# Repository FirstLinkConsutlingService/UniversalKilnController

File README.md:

# UniversalKilnController
A Hardware/Software project to control devices of the KILN persuasion ( temperature and cooking time manager) 

Test1

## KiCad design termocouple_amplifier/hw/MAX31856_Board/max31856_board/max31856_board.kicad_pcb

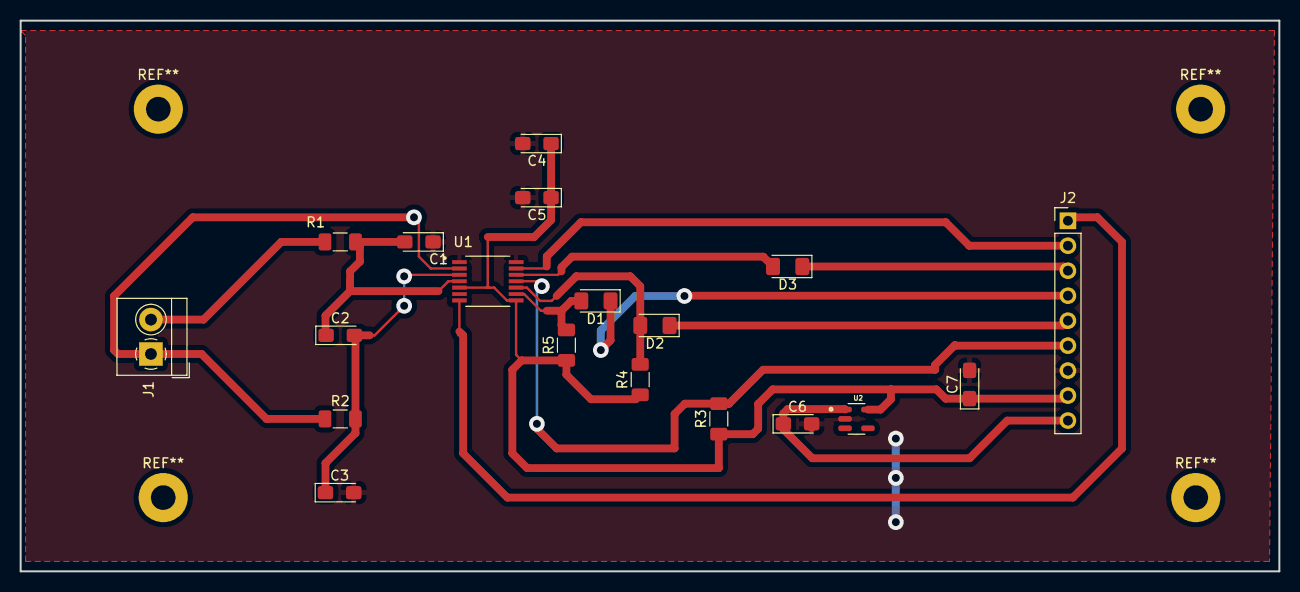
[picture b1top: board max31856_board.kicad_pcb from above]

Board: 2 copper layers, 128.0 x 56.0 mm, 19 parts (0 on the bottom side), 16 nets.

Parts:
C1, C3: 0.01uF; CP_EIA-3216-10_Kemet-I_Pad1.58x1.35mm_HandSolder
C2, C4, C5: 0.1uF; CP_EIA-3216-10_Kemet-I_Pad1.58x1.35mm_HandSolder
C6, C7: 10uF; CP_EIA-3216-10_Kemet-I_Pad1.58x1.35mm_HandSolder
D1, D2, D3: 1N4148; D_1206_3216Metric_Pad1.42x1.75mm_HandSolder
J1: Screw_Terminal_01x02; TerminalBlock_4Ucon_1x02_P3.50mm_Horizontal
J2: Conn_01x09_Male; PinHeader_1x09_P2.54mm_Vertical
R1, R2: 100; R_1206_3216Metric_Pad1.30x1.75mm_HandSolder
R3, R4, R5: 10K; R_1206_3216Metric_Pad1.30x1.75mm_HandSolder
U1: MAX31856MUD+T; SOP65P640X110-14N
U2: MIC5225-3.3YM5-TR; SOT95P280X145-5N

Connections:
+3.3V: C4.1, C5.1, C7.1, J2.8, R3.1, R4.1, R5.1, U1.5 (AVDD), U1.8 (DVDD), U2.5 (OUT)
/SCK: D2.1 (K), J2.5
/SDI: D3.1 (K), J2.3
/SDO: J2.6, R3.2, U1.11 (SDO)
/T+: C1.2, C2.1, R1.2, U1.4 (T+)
/T-: C2.2, C3.1, R2.2, U1.3 (T-)
/THERM-: J1.1, R2.1, U1.2 (BIAS)
/VIN: C6.1, J2.9, U2.1 (IN), U2.3 (EN)
/~CS: D1.1 (K), J2.4
/~DRDY: J2.1, U1.7 (~DRDY)
/~FAULT: J2.2, U1.13 (~FAULT)
GNDD: C1.1, C3.2, C4.2, C5.2, C6.2, C7.2, J2.7, U1.1 (AGND), U1.14 (DGND), U2.2 (GND)
unnamed: D1.2 (A), R5.2, U1.9 (~CS)
unnamed: D2.2 (A), R4.2, U1.10 (SCK)
unnamed: D3.2 (A), U1.12 (SDI)
unnamed: J1.2, R1.1

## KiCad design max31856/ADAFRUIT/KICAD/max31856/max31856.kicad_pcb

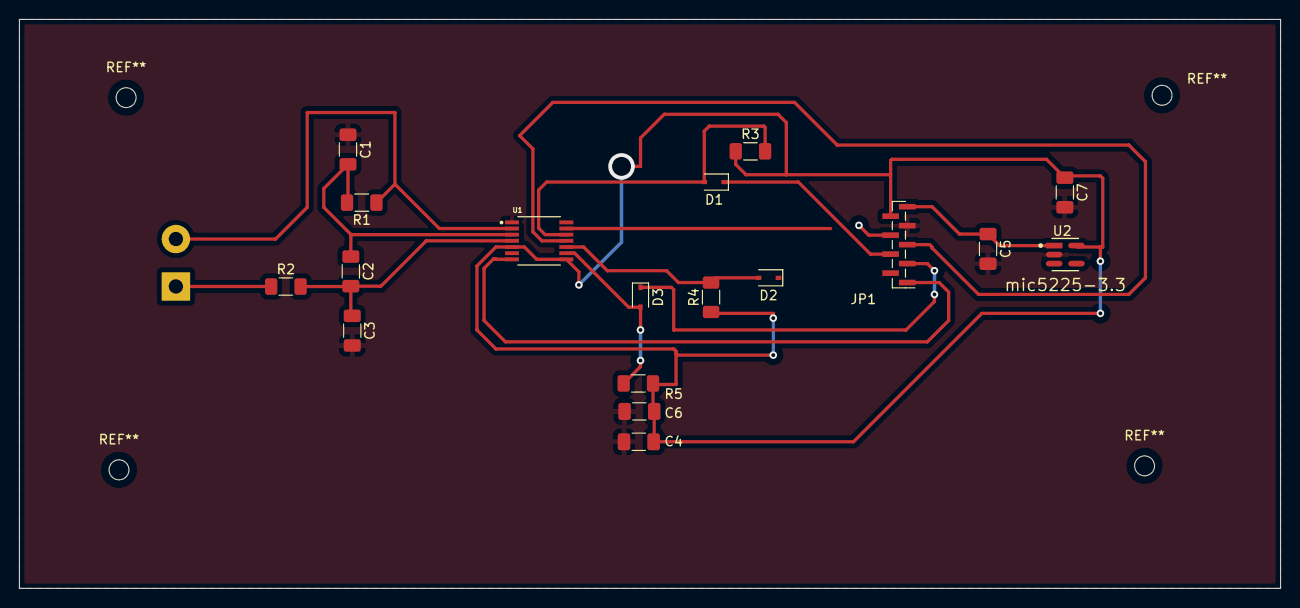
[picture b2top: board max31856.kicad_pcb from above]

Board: 2 copper layers, 133.0 x 60.0 mm, 19 parts (1 on the bottom side), 16 nets.

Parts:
C1, C2, C3: 0.01uF; C_1206_3216Metric_Pad1.33x1.80mm_HandSolder
C4, C6: 0.1uF; C_1206_3216Metric_Pad1.33x1.80mm_HandSolder
C5, C7: 10uF; C_1206_3216Metric_Pad1.33x1.80mm_HandSolder
D1, D2, D3: 1N4148; D_SOD-323
JP1: HEADER-1X970MIL; PinHeader_1x09_P1.00mm_Vertical_SMD_Pin1Left
R1, R2: 100; R_1206_3216Metric_Pad1.30x1.75mm_HandSolder
R3, R4, R5: 10K; R_1206_3216Metric_Pad1.30x1.75mm_HandSolder
U1: MAX31856; SOP65P640X110-14N
U2: mic5225-3.3; Microchip_Technology-SOT23-5LD-PL-1-0-0-IPC_A
X1: 3.5mm term; Altech_AK300_1x02_P5.00mm_45-Degree

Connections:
+3V3: C4.1, C6.1, C7.1, JP1.8, R3.1, R4.1, R5.1, U1.5 (AVDD), U1.8 (DVDD), U2.5 (OUT)
/DRDY: JP1.1, U1.7 (~DRDY)
GNDD: C1.1, C3.2, C4.2, C5.2, C6.2, C7.2, JP1.7, U1.1 (AGND), U2.2 (GND)
unnamed: C1.2, C2.1, R1.2, U1.3 (T-)
unnamed: C2.2, C3.1, R2.2, U1.4 (T+)
unnamed: D1.1 (K), JP1.4
unnamed: D1.2 (A), R3.2, U1.12 (SDI)
unnamed: D2.1 (K), JP1.6 (2)
unnamed: D2.2 (A), R4.2, U1.10 (SCK)
unnamed: D3.1 (K), JP1.3
unnamed: D3.2 (A), R5.2, U1.9 (~CS)
unnamed: JP1.2 (6), U1.13 (~FAULT)
unnamed: JP1.5, U1.11 (SDO)
unnamed: R1.1, U1.2 (BIAS), X1.2
unnamed: R2.1, X1.1
VDD: C5.1, JP1.9, U2.1 (IN), U2.3 (EN)

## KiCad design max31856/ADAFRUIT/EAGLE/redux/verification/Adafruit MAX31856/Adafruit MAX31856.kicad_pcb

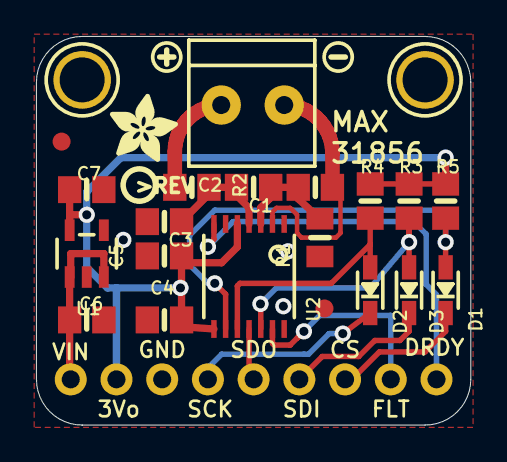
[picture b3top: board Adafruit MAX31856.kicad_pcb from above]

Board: 2 copper layers, 24.1 x 21.6 mm, 28 parts (1 on the bottom side), 16 nets.

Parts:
C1: 0.01uF; 0805_10MGAP
C2, C4, C5: 0.1uF; 0805-NO
C3: 0.01uF; 0805-NO
C6, C7: 10uF; 0805-NO
D1, D2, D3: 1N4148; SOD-323
FID1, FID2: FIDUCIAL""; FIDUCIAL_1MM
JP1: 1X09_ROUND_70
R1, R2: 100; 0805-NO
R3, R4, R5: 10K; 0805-NO
U1: mic5225-3.3; SOT23-5
U2: MAX31856; TSSOP14
U$1: PCBFEAT-REV-040
U$13, U$14: MOUNTINGHOLE2.5; MOUNTINGHOLE_2.5_PLATED
U$23: SYMBOL_PLUS
U$24: SYMBOL_MINUS
U$25: ADAFRUIT_3.5MM
U$26: ADAFRUIT_TEXT_20MM
X1: 3.5mm term; TERMBLOCK_1X2-3.5MM

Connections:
3.3V: C4.1, C5.1, C7.1, JP1.8, R3.2, R4.2, R5.2, U1.5, U2.5, U2.8
DRDY: JP1.1, U2.7
GND: C1.1, C3.2, C4.2, C5.2, C6.2, C7.2, JP1.7, U1.2, U2.1, U2.14
SCK: D2.C, JP1.6
SCK_3V: D2.A, R4.1, U2.10
SDI: D3.C, JP1.4
SDO: JP1.5, U2.11
SDO_3V: D3.A, R3.1, U2.12
T+: C2.2, C3.1, R2.2, U2.4
T-: C1.2, C2.1, R1.2, U2.3
THERM+: R2.1, X1.1
THERM-: R1.1, U2.2, X1.2
VIN: C6.1, JP1.9, U1.1, U1.3
~CS_3V: D1.A, R5.1, U2.9
~CS: D1.C, JP1.3
~FAULT: JP1.2, U2.13

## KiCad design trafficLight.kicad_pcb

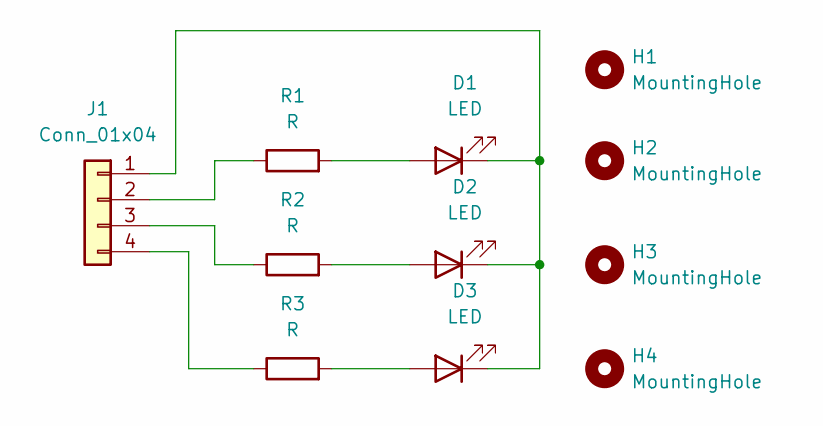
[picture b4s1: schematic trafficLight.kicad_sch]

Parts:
D1, D2, D3: LED; LED_D5.0mm
H1, H2, H3, H4: MountingHole; MountingHole_2.5mm
J1: Conn_01x04; JST_PH_B4B-PH-K_1x04_P2.00mm_Vertical
R1, R2, R3: R; R_Axial_DIN0207_L6.3mm_D2.5mm_P10.16mm_Horizontal

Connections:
unnamed: D1.1 (K), D2.1 (K), D3.1 (K), J1.1
unnamed: D1.2 (A), R1.2
unnamed: D2.2 (A), R2.2
unnamed: D3.2 (A), R3.2
unnamed: J1.2, R1.1
unnamed: J1.3, R2.1
unnamed: J1.4, R3.1

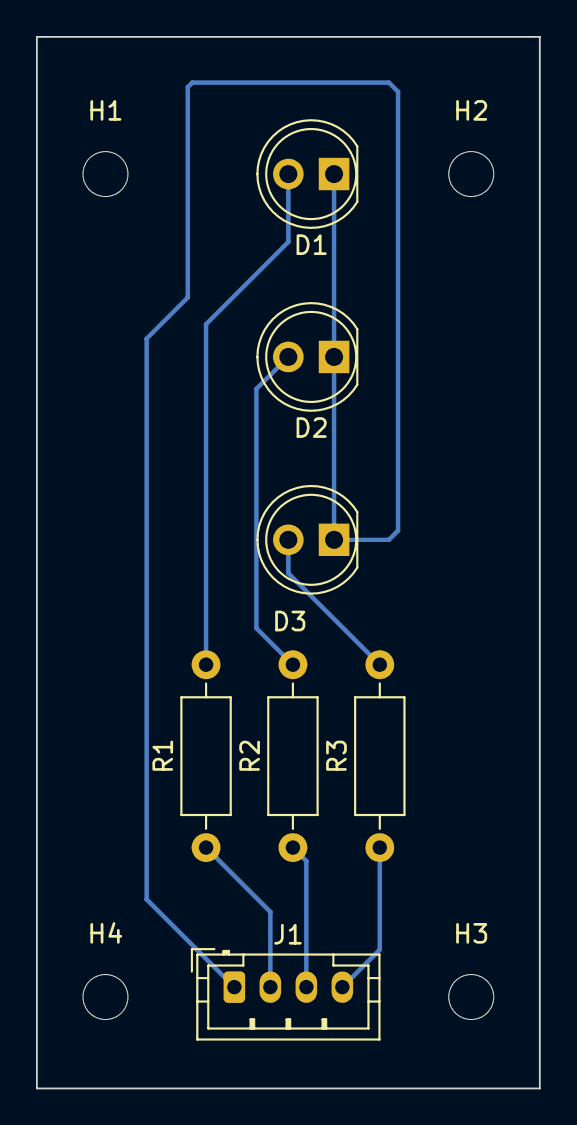
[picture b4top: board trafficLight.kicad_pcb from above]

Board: 2 copper layers, 27.9 x 58.4 mm, 11 parts (0 on the bottom side), 7 nets.

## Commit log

2022-02-09 Added a line for testing push
2022-02-09 Added WIP for trafficlight
2022-02-18 Added pcb ( WIP)
2022-02-18 Added a project to show progress in the tutorial
2022-03-04 Recent modicifation of layout
    i deleted: trafficLight-backups/trafficLight-2022-02-05_192826.zip
2022-03-04 Added the gerber files
2022-04-13 Put the trace on the back side
2022-04-13 Added Gerbers abd Drill - most of those files are generated and therefore should be in the .ignore files since I am still unfamiliar with what is required to be kept I checked everything in.
2022-04-13 Save latest version
2022-05-18 Added a simple pwm program for test
2022-09-14 Baseline Max31856
2022-11-11 Added the latest of the Max31856 FLCS board design
